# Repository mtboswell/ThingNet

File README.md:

ThingNet is a tiny breakout board for an ESP8266-12 that is intended to reduce the cost and difficulty of connecting a Thing to the 'Net.

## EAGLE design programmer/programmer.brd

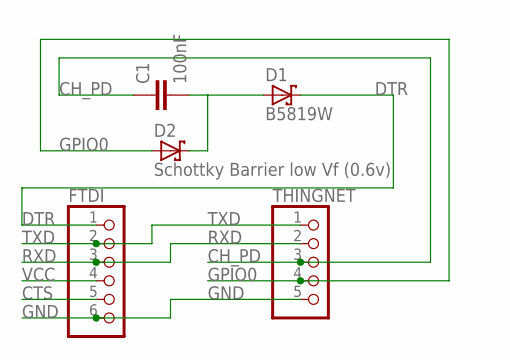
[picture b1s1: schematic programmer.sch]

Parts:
C1: 100nF; C025-024X044
D1: B5819W; DO35-7
D2: Schottky Barrier low Vf (0.6v); DO35-7
FTDI: PINHD-1X6; 1X06
THINGNET: PINHD-1X5; 1X05

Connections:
CH_PD: C1.1, THINGNET.3
CTS: FTDI.5
DTR: D1.C, FTDI.1
GND: FTDI.6, THINGNET.5
GPIO0: D2.A, THINGNET.4
unnamed: C1.2, D1.A, D2.C
RXD: FTDI.3, THINGNET.2
TXD: FTDI.2, THINGNET.1
VCC: FTDI.4

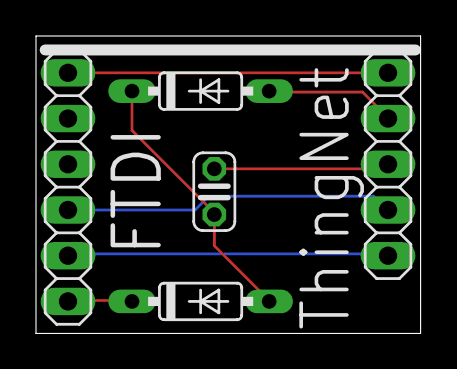
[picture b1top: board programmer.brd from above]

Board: 2 copper layers, 21.4 x 16.5 mm, 5 parts (0 on the bottom side), 7 nets.

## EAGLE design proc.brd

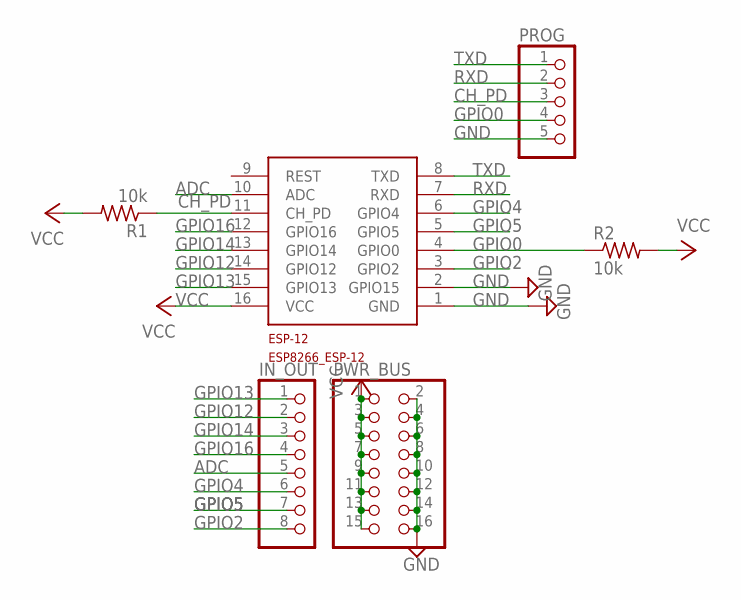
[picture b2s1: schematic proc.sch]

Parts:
ESP-12: ESP8266_ESP-12; ESP8266-ESP12
IN_OUT: PINHD-1X8; 1X08
PROG: PINHD-1X5; 1X05
PWR_BUS: PINHD-2X8; 2X08
R1, R2: 10k; M1206

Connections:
ADC: ESP-12.10 (ADC), IN_OUT.5
CH_PD: ESP-12.11 (CH_PD), PROG.3, R1.1
GND: ESP-12.1 (GND), ESP-12.2 (GPIO15), PROG.5, PWR_BUS.2, PWR_BUS.4, PWR_BUS.6, PWR_BUS.8, PWR_BUS.10, PWR_BUS.12, PWR_BUS.14, PWR_BUS.16
GPIO0: ESP-12.4 (GPIO0), PROG.4, R2.1
GPIO2: ESP-12.3 (GPIO2), IN_OUT.8
GPIO4: ESP-12.6 (GPIO4), IN_OUT.6
GPIO5: ESP-12.5 (GPIO5), IN_OUT.7
GPIO12: ESP-12.14 (GPIO12), IN_OUT.2
GPIO13: ESP-12.15 (GPIO13), IN_OUT.1
GPIO14: ESP-12.13 (GPIO14), IN_OUT.3
GPIO16: ESP-12.12 (GPIO16), IN_OUT.4
RXD: ESP-12.7 (RXD), PROG.2
TXD: ESP-12.8 (TXD), PROG.1
VCC: ESP-12.16 (VCC), PWR_BUS.1, PWR_BUS.3, PWR_BUS.5, PWR_BUS.7, PWR_BUS.9, PWR_BUS.11, PWR_BUS.13, PWR_BUS.15, R1.2, R2.2

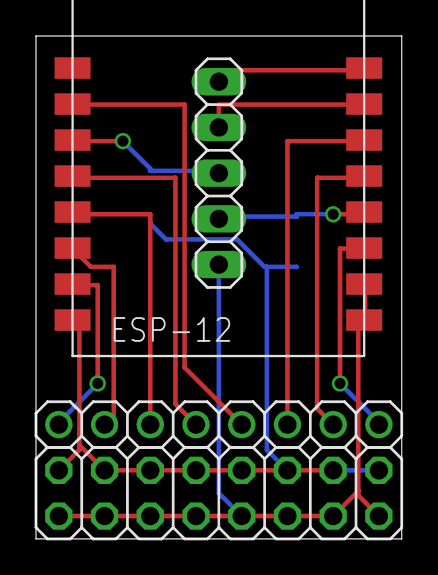
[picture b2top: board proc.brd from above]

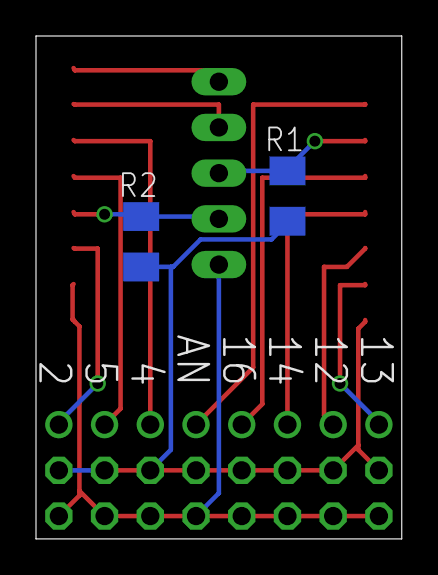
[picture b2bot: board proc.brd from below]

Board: 2 copper layers, 20.3 x 27.9 mm, 6 parts (2 on the bottom side), 14 nets.

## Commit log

2016-09-27 Updated programmer board and organized everything into folders
2017-03-26 Added netpwr, AQH2223 lib, datasheets
